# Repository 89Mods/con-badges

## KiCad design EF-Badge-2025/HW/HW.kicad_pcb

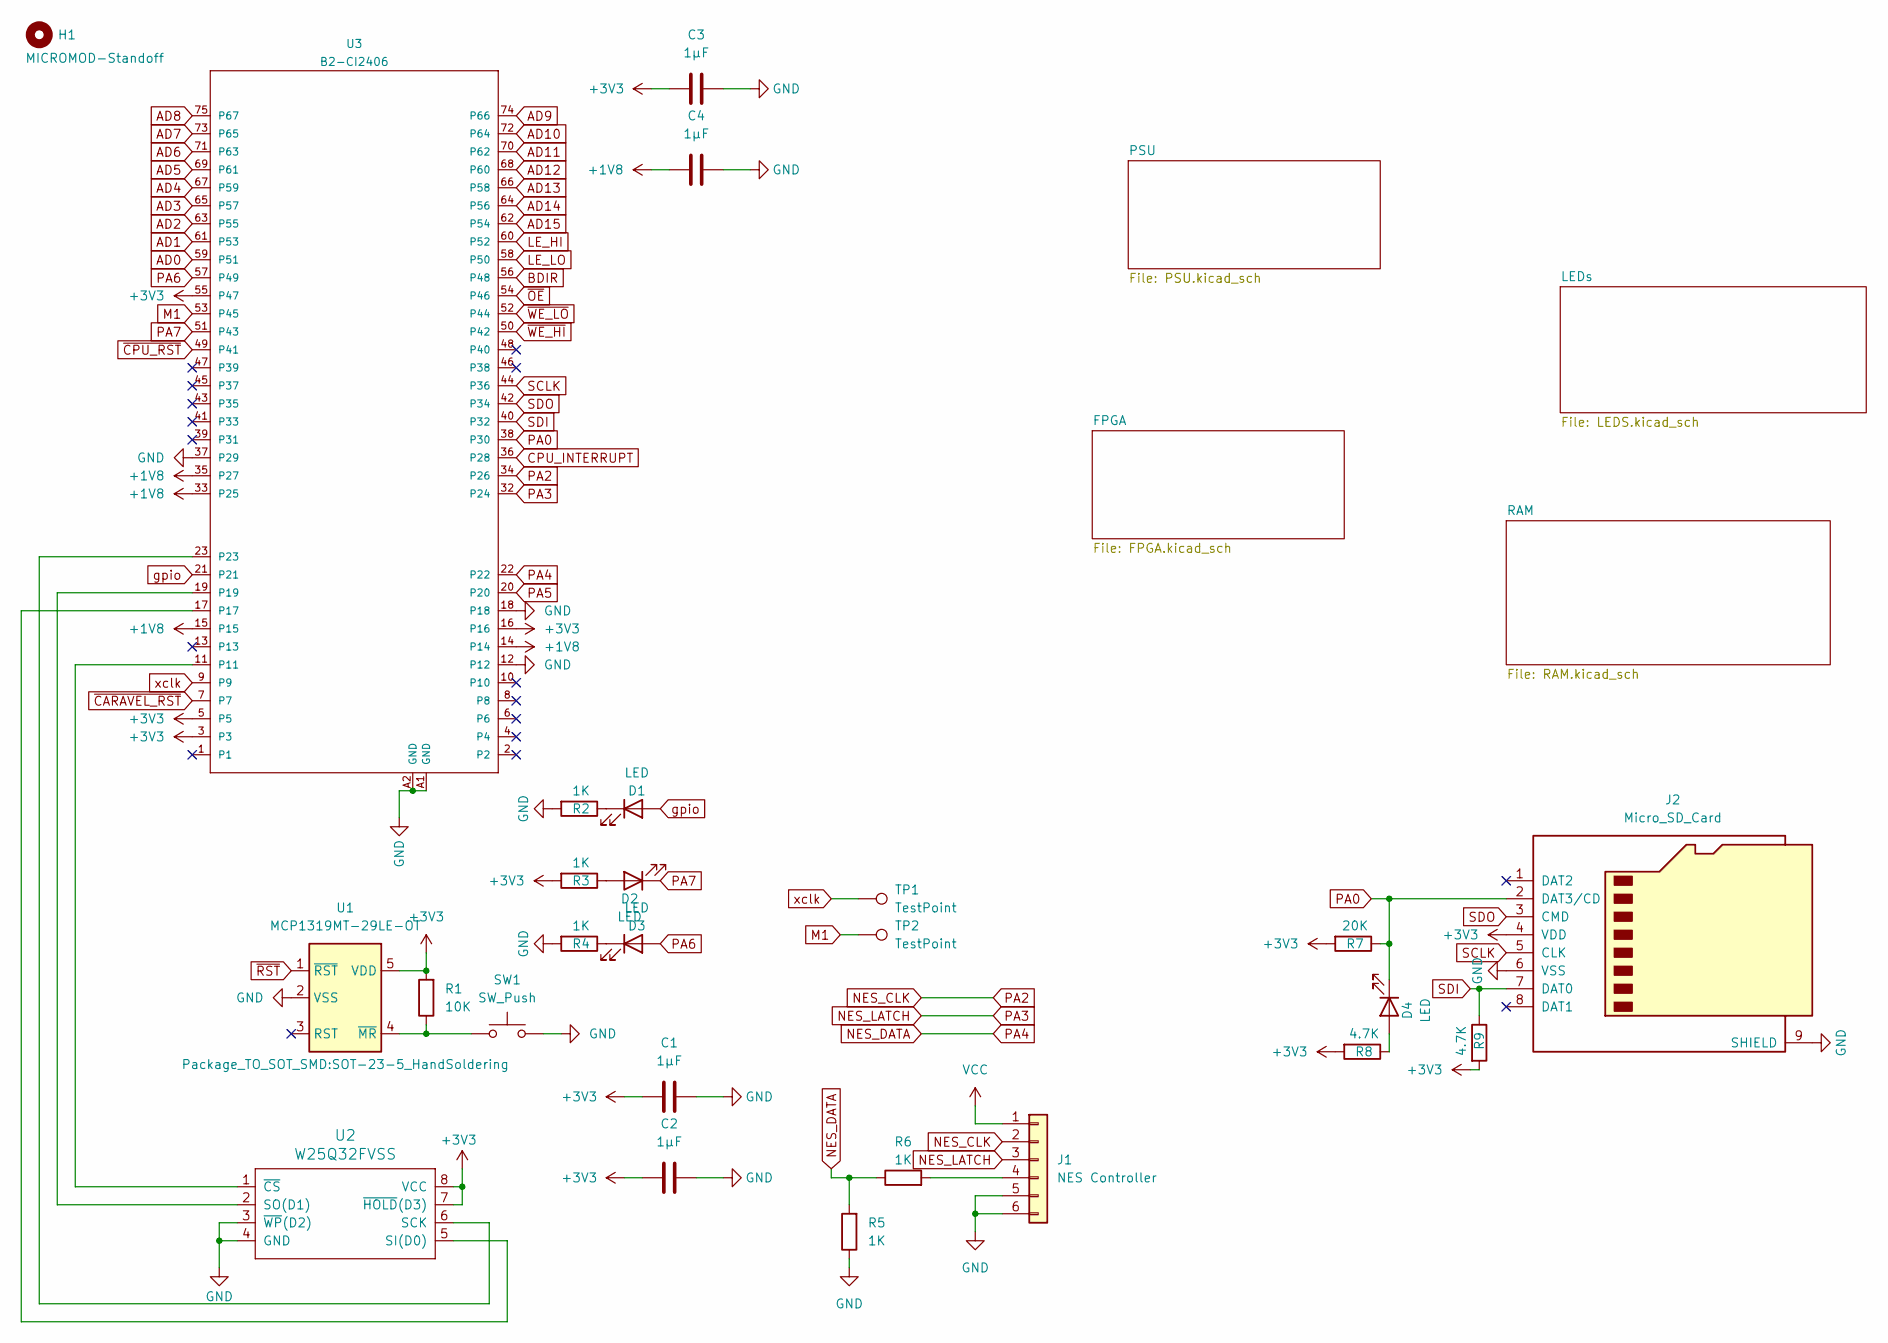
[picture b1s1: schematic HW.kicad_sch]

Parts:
C1, C2, C3, C4: 1µF; C_0805_2012Metric_Pad1.18x1.45mm_HandSolder
D1, D2, D3, D4: LED; LED_1206_3216Metric_Pad1.42x1.75mm_HandSolder
H1: MICROMOD-Standoff; MicroMod-Standoff
J1: NES Controller; PinSocket_1x06_P2.54mm_Vertical
J2: Micro_SD_Card; microSD_HC_Hirose_DM3AT-SF-PEJM5
R1: 10K; R_1206_3216Metric_Pad1.30x1.75mm_HandSolder
R2, R3, R4, R5, R6: 1K; R_1206_3216Metric_Pad1.30x1.75mm_HandSolder
R7: 20K; R_1206_3216Metric_Pad1.30x1.75mm_HandSolder
R8, R9: 4.7K; R_1206_3216Metric_Pad1.30x1.75mm_HandSolder
SW1: SW_Push; SW_PUSH_6mm
TP1, TP2: TestPoint; TestPoint_Pad_D1.0mm
U1: MCP1319MT-29LE-OT; SOT-23-5_HandSoldering
U2: W25Q32FVSS; DIP-8_W7.62mm; Part # W25Q32JVSSIQ
U3: B2-CI2406; M.2-CONNECTOR-E

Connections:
+1V8: C4.1, U3.14, U3.15, U3.33 (P25), U3.35 (P27); also elsewhere on the board
+3V3: C1.1, C2.1, C3.1, J2.4 (VDD), R1.2, R3.2, R7.2, R8.2, R9.2, U1.5 (VDD), U2.7 (~HOLD(D3)), U2.8 (VCC), U3.3, U3.5, U3.16, U3.55 (P47); also elsewhere on the board
AD0: U3.59 (P51); also elsewhere on the board
AD1: U3.61 (P53); also elsewhere on the board
AD2: U3.63 (P55); also elsewhere on the board
AD3: U3.65 (P57); also elsewhere on the board
AD4: U3.67 (P59); also elsewhere on the board
AD5: U3.69 (P61); also elsewhere on the board
AD6: U3.71 (P63); also elsewhere on the board
AD7: U3.73 (P65); also elsewhere on the board
AD8: U3.75 (P67); also elsewhere on the board
AD9: U3.74 (P66); also elsewhere on the board
AD10: U3.72 (P64); also elsewhere on the board
AD11: U3.70 (P62); also elsewhere on the board
AD12: U3.68 (P60); also elsewhere on the board
AD13: U3.66 (P58); also elsewhere on the board
AD14: U3.64 (P56); also elsewhere on the board
AD15: U3.62 (P54); also elsewhere on the board
BDIR: U3.56 (P48)
CPU_INTERRUPT: U3.36 (P28); also elsewhere on the board
GND: C1.2, C2.2, C3.2, C4.2, J1.5, J1.6, J2.6 (VSS), J2.9 (SHIELD), R2.2, R4.2, R5.1, SW1.2, U1.2 (VSS), U2.3 (~WP(D2)), U2.4 (GND), U3.12, U3.18, U3.37 (P29), U3.A1 (GND), U3.A2 (GND); also elsewhere on the board
LE_HI: U3.60 (P52); also elsewhere on the board
LE_LO: U3.58 (P50); also elsewhere on the board
M1: TP2.1, U3.53 (P45)
NES_CLK: J1.2, U3.34 (P26)
NES_DATA: R5.2, R6.1, U3.22
NES_LATCH: J1.3, U3.32 (P24)
unnamed: D1.1 (K), R2.1
unnamed: D2.2 (A), R3.1
unnamed: D3.1 (K), R4.1
unnamed: D4.2 (A), R8.1
unnamed: J1.4, R6.2
unnamed: R1.1, SW1.1, U1.4 (~MR)
unnamed: U2.6 (SCK), U3.23
unnamed: U2.5 (SI(D0)), U3.17
unnamed: U2.2 (SO(D1)), U3.19
unnamed: U2.1 (~CS), U3.11
PA0: D4.1 (K), J2.2 (DAT3/CD), R7.1, U3.38 (P30)
PA5: U3.20
PA6: D3.2 (A), U3.57 (P49)
PA7: D2.1 (K), U3.51 (P43)
SCLK: J2.5 (CLK), U3.44 (P36)
SDI: J2.7 (DAT0), R9.1, U3.40 (P32)
SDO: J2.3 (CMD), U3.42 (P34)
VCC: J1.1; also elsewhere on the board
gpio: D1.2 (A), U3.21; also elsewhere on the board
xclk: TP1.1, U3.9; also elsewhere on the board
~CARAVEL_RST: U3.7; also elsewhere on the board
~CPU_RST: U3.49 (P41); also elsewhere on the board
~OE: U3.54 (P46); also elsewhere on the board
~RST: U1.1 (~RST); also elsewhere on the board
~WE_HI: U3.50 (P42); also elsewhere on the board
~WE_LO: U3.52 (P44); also elsewhere on the board

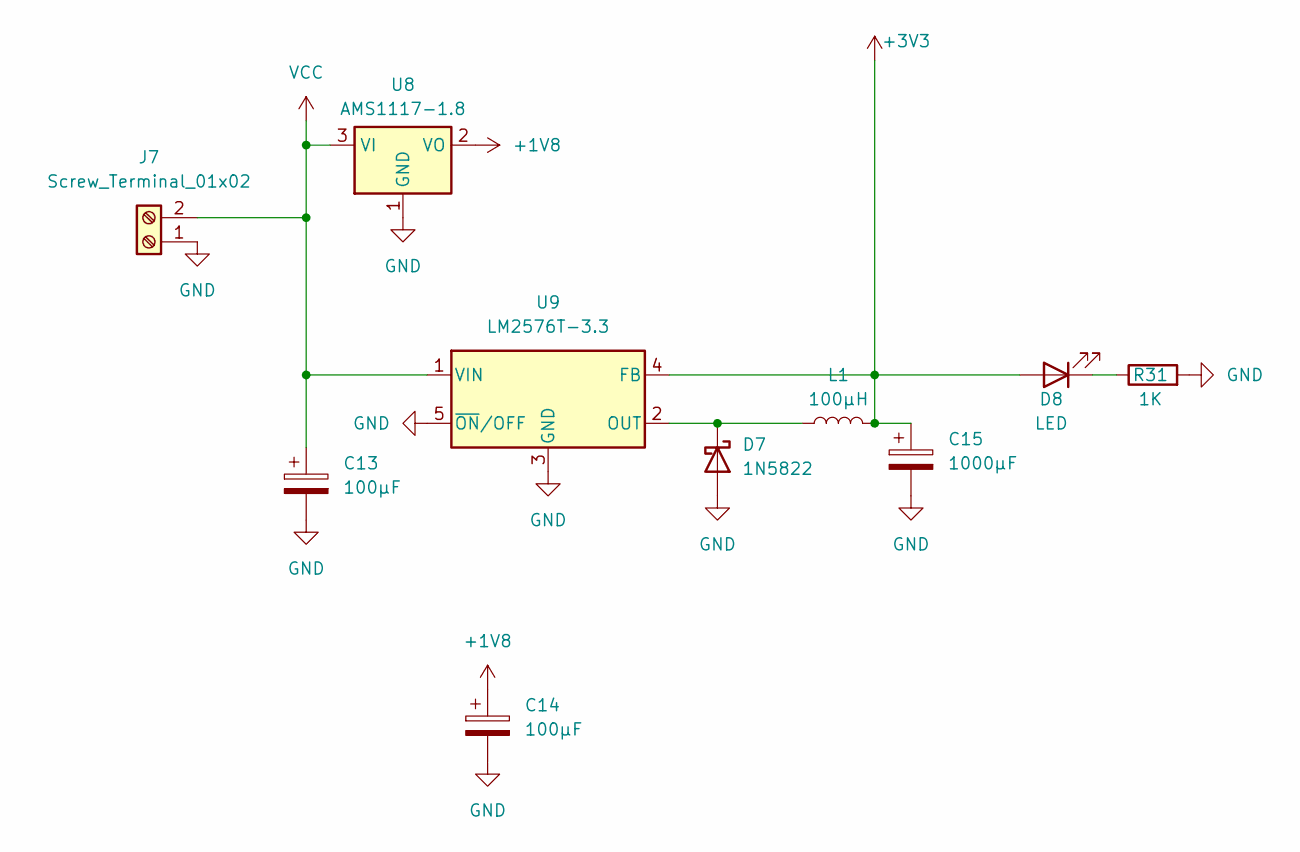
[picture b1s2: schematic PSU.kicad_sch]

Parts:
C13: 100µF; CP_Radial_D5.0mm_P2.50mm
C14: 100µF; CP_Elec_4x3
C15: 1000µF; CP_Radial_D6.3mm_P2.50mm
D7: 1N5822; D_DO-201AD_P15.24mm_Horizontal
D8: LED; LED_1206_3216Metric_Pad1.42x1.75mm_HandSolder
J7: Screw_Terminal_01x02; TerminalBlock_bornier-2_P5.08mm
L1: 100µH; L_Radial_D6.0mm_P4.00mm
R31: 1K; R_1206_3216Metric_Pad1.30x1.75mm_HandSolder
U8: AMS1117-1.8; SOT-223-3_TabPin2
U9: LM2576T-3.3; TO-220-5_Horizontal_TabDown_Fixed

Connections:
+1V8: C14.1, U8.2 (VO); also elsewhere on the board
+3V3: C15.1, D8.2 (A), L1.2, U9.4 (FB); also elsewhere on the board
GND: C13.2, C14.2, C15.2, D7.2 (A), J7.1, R31.2, U8.1 (GND), U9.3 (GND), U9.5 (~ON/OFF); also elsewhere on the board
unnamed: D7.1 (K), L1.1, U9.2 (OUT)
unnamed: D8.1 (K), R31.1
VCC: C13.1, J7.2, U8.3 (VI), U9.1 (VIN); also elsewhere on the board

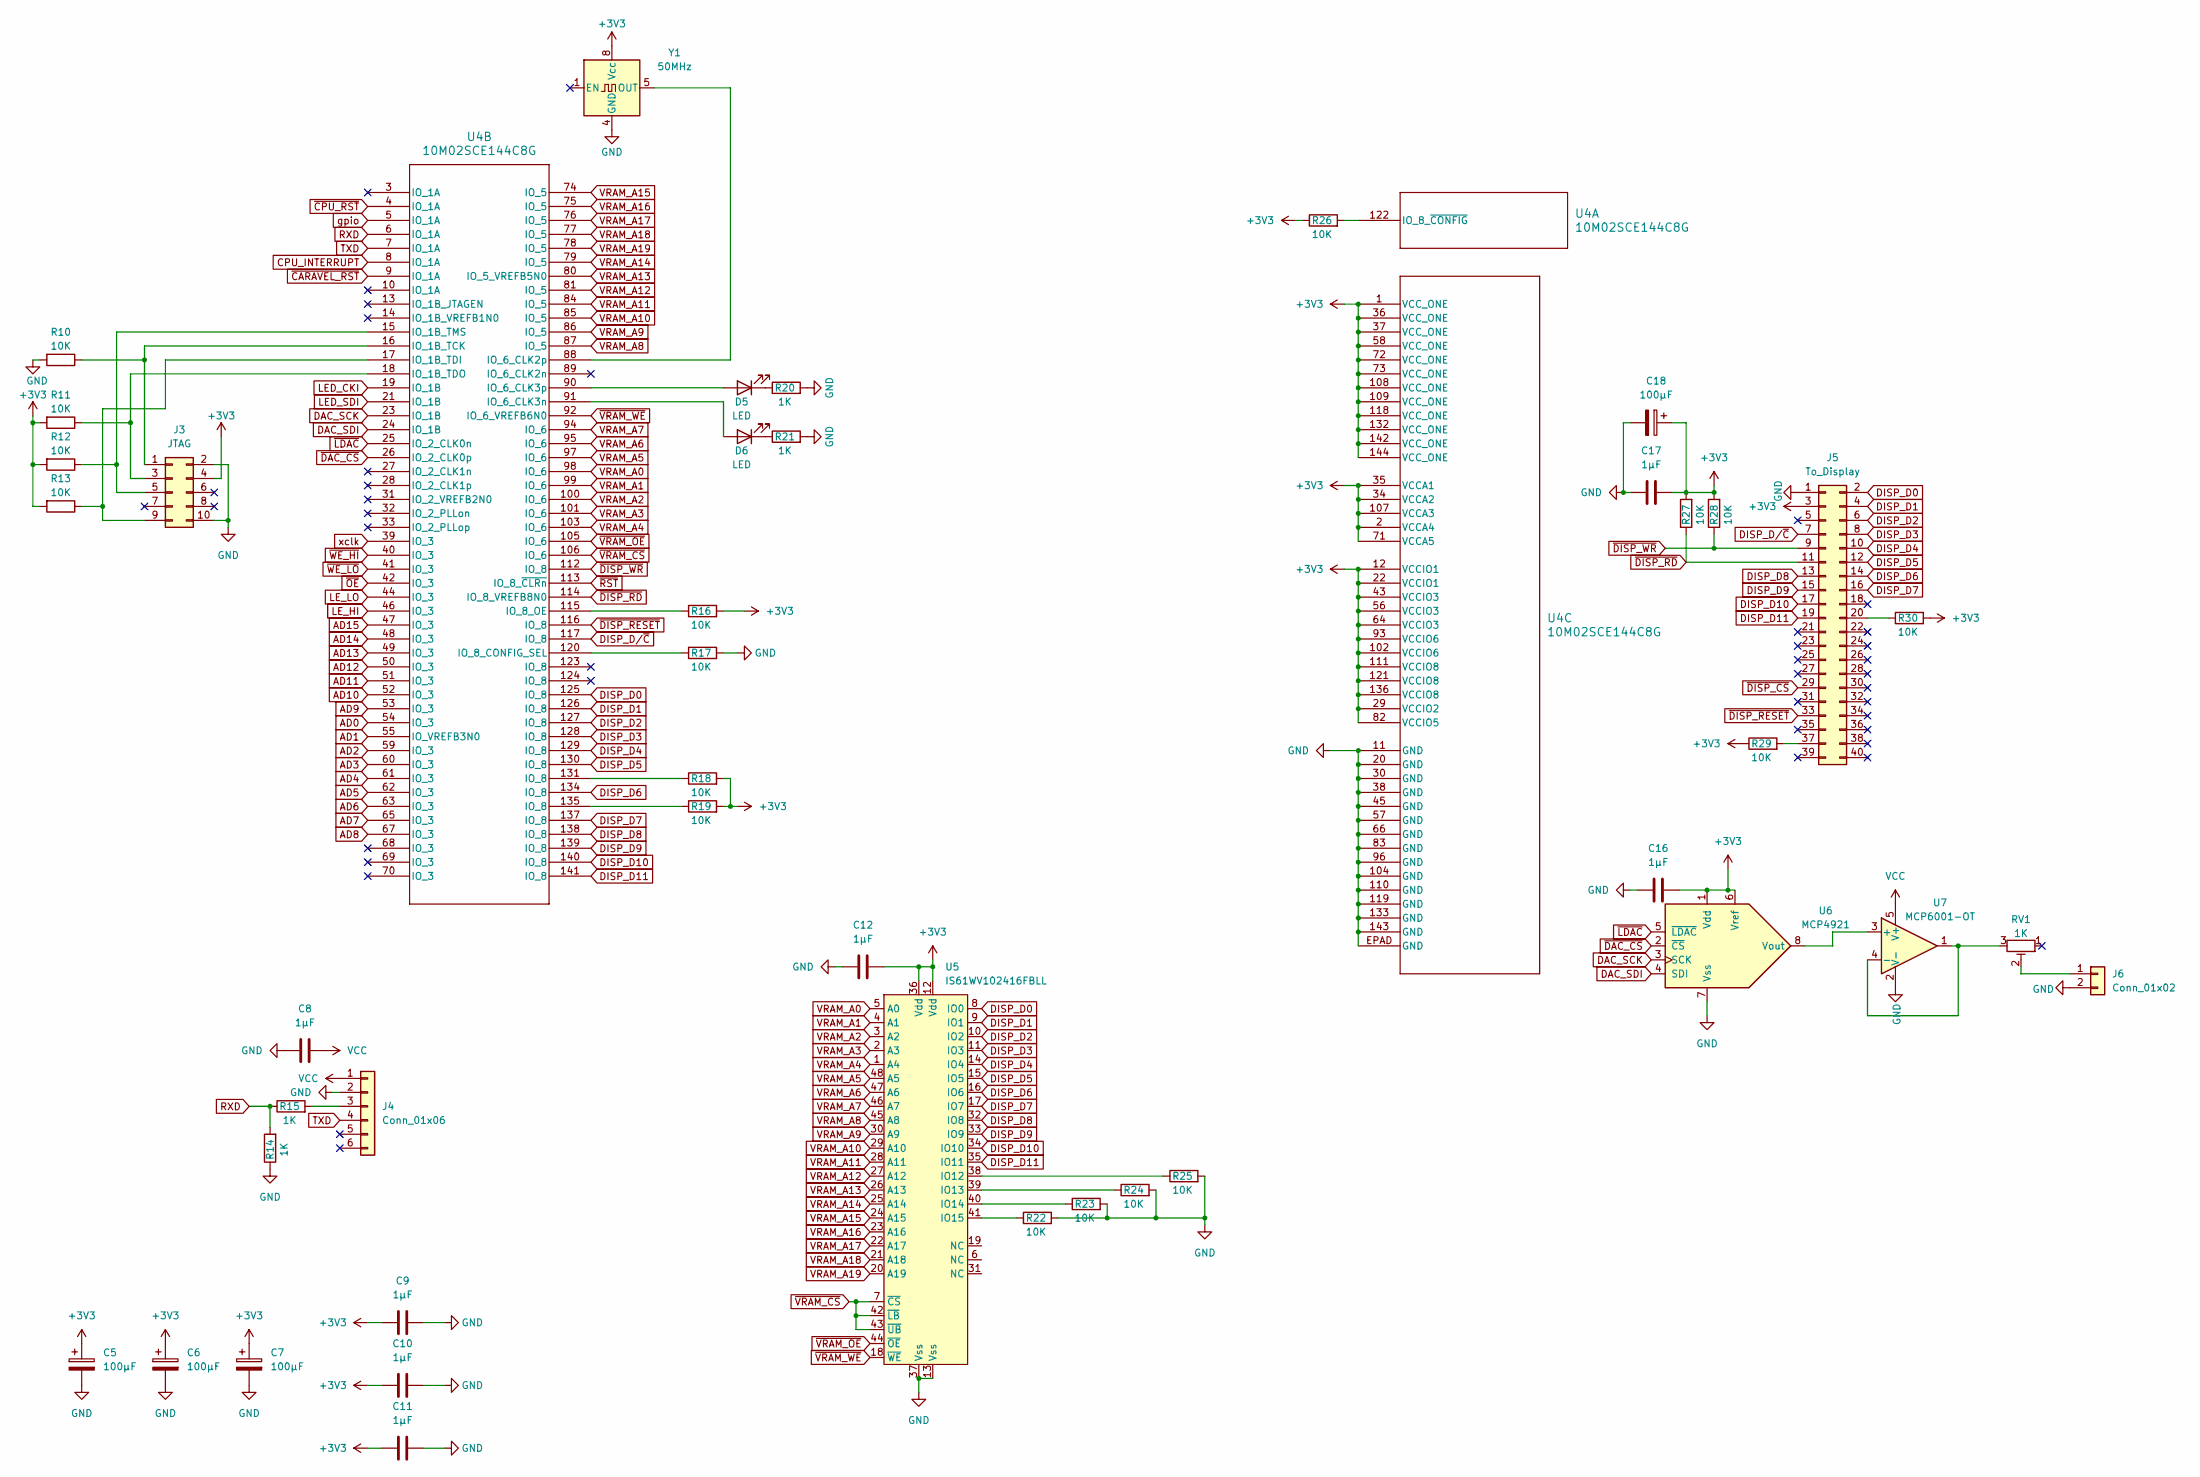
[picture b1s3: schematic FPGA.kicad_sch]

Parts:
C5, C6, C7, C18: 100µF; CP_Elec_4x3
C8, C9, C10, C11, C12, C16, C17: 1µF; C_0805_2012Metric_Pad1.18x1.45mm_HandSolder
D5, D6: LED; LED_1206_3216Metric_Pad1.42x1.75mm_HandSolder
J3: JTAG; PinHeader_2x05_P2.54mm_Vertical
J4: Conn_01x06; PinSocket_1x06_P2.54mm_Vertical
J5: To_Display; PinHeader_2x20_P2.54mm_Vertical
J6: Conn_01x02; PinHeader_1x02_P2.54mm_Vertical
R10, R11, R12, R13, R16, R17, R18, R19, R22, R23, R24, R25, R26, R27, R28, R29, R30: 10K; R_1206_3216Metric_Pad1.30x1.75mm_HandSolder
R14, R15, R20, R21: 1K; R_1206_3216Metric_Pad1.30x1.75mm_HandSolder
RV1: 1K; Potentiometer_ACP_CA9-V10_Vertical
U4: 10M02SCE144C8G; EQFP144_A-1.65-D2-4.0_INT
U5: IS61WV102416FBLL; TSOP-I-48_18.4x12mm_P0.5mm; Mouser 870-61WV12416FBL1TLI
U6: MCP4921; DIP-8_W7.62mm
U7: MCP6001-OT; SOT-23-5
Y1: 50MHz; Oscillator_DIP-8

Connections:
+3V3: C5.1, C6.1, C7.1, C9.1, C10.1, C11.1, C12.2, C16.2, C17.2, C18.1, J3.4, J5.3, R11.2, R12.2, R13.2, R16.2, R18.2, R19.2, R26.1, R27.2, R28.2, R29.1, R30.2, U4.1 (VCC_ONE), U4.2 (VCCA4), U4.12 (VCCIO1), U4.22 (VCCIO1), U4.29 (VCCIO2), U4.34 (VCCA2), U4.35 (VCCA1), U4.36 (VCC_ONE), U4.37 (VCC_ONE), U4.43 (VCCIO3), U4.56 (VCCIO3), U4.58 (VCC_ONE), U4.64 (VCCIO3), U4.71 (VCCA5), U4.72 (VCC_ONE), U4.73 (VCC_ONE), U4.82 (VCCIO5), U4.93 (VCCIO6), U4.102 (VCCIO6), U4.107 (VCCA3), U4.108 (VCC_ONE), U4.109 (VCC_ONE), U4.111 (VCCIO8), U4.118 (VCC_ONE), U4.121 (VCCIO8), U4.132 (VCC_ONE), U4.136 (VCCIO8), U4.142 (VCC_ONE), U4.144 (VCC_ONE), U5.12 (Vdd), U5.36 (Vdd), U6.1 (Vdd), U6.6 (Vref), Y1.8 (Vcc); also elsewhere on the board
AD0: U4.54 (IO_3); also elsewhere on the board
AD1: U4.55 (IO_VREFB3N0); also elsewhere on the board
AD2: U4.59 (IO_3); also elsewhere on the board
AD3: U4.60 (IO_3); also elsewhere on the board
AD4: U4.61 (IO_3); also elsewhere on the board
AD5: U4.62 (IO_3); also elsewhere on the board
AD6: U4.63 (IO_3); also elsewhere on the board
AD7: U4.65 (IO_3); also elsewhere on the board
AD8: U4.67 (IO_3); also elsewhere on the board
AD9: U4.53 (IO_3); also elsewhere on the board
AD10: U4.52 (IO_3); also elsewhere on the board
AD11: U4.51 (IO_3); also elsewhere on the board
AD12: U4.50 (IO_3); also elsewhere on the board
AD13: U4.49 (IO_3); also elsewhere on the board
AD14: U4.48 (IO_3); also elsewhere on the board
AD15: U4.47 (IO_3); also elsewhere on the board
CPU_INTERRUPT: U4.8 (IO_1A); also elsewhere on the board
DAC_SCK: U4.23 (IO_1B), U6.3 (SCK)
DAC_SDI: U4.24 (IO_1B), U6.4 (SDI)
DISP_D0: J5.2, U4.125 (IO_8), U5.8 (IO0)
DISP_D1: J5.4, U4.126 (IO_8), U5.9 (IO1)
DISP_D2: J5.6, U4.127 (IO_8), U5.10 (IO2)
DISP_D3: J5.8, U4.128 (IO_8), U5.11 (IO3)
DISP_D4: J5.10, U4.129 (IO_8), U5.14 (IO4)
DISP_D5: J5.12, U4.130 (IO_8), U5.15 (IO5)
DISP_D6: J5.14, U4.134 (IO_8), U5.16 (IO6)
DISP_D7: J5.16, U4.137 (IO_8), U5.17 (IO7)
DISP_D8: J5.13, U4.138 (IO_8), U5.32 (IO8)
DISP_D9: J5.15, U4.139 (IO_8), U5.33 (IO9)
DISP_D10: J5.17, U4.140 (IO_8), U5.34 (IO10)
DISP_D11: J5.19, U4.141 (IO_8), U5.35 (IO11)
DISP_D/~C: J5.7, U4.117 (IO_8)
GND: C5.2, C6.2, C7.2, C8.1, C9.2, C10.2, C11.2, C12.1, C16.1, C17.1, C18.2, J3.2, J3.10, J4.2, J5.1, J6.2, R10.2, R14.1, R17.2, R20.2, R21.2, R22.2, R23.2, R24.2, R25.2, U4.11 (GND), U4.20 (GND), U4.30 (GND), U4.38 (GND), U4.45 (GND), U4.57 (GND), U4.66 (GND), U4.83 (GND), U4.96 (GND), U4.104 (GND), U4.110 (GND), U4.119 (GND), U4.133 (GND), U4.143 (GND), U4.EPAD (GND), U5.13 (Vss), U5.37 (Vss), U6.7 (Vss), U7.2 (V-), Y1.4 (GND); also elsewhere on the board
LED_CKI: U4.19 (IO_1B); also elsewhere on the board
LED_SDI: U4.21 (IO_1B); also elsewhere on the board
LE_HI: U4.46 (IO_3); also elsewhere on the board
LE_LO: U4.44 (IO_3); also elsewhere on the board
unnamed: D5.2 (A), U4.90 (IO_6_CLK3p)
unnamed: D5.1 (K), R20.1
unnamed: D6.2 (A), U4.91 (IO_6_CLK3n)
unnamed: D6.1 (K), R21.1
unnamed: J3.1, R10.1, U4.16 (IO_1B_TCK)
unnamed: J3.3, R11.1, U4.18 (IO_1B_TDO)
unnamed: J3.5, R12.1, U4.15 (IO_1B_TMS)
unnamed: J3.9, R13.1, U4.17 (IO_1B_TDI)
unnamed: J4.3, R15.2
unnamed: J5.20, R30.1
unnamed: J5.37, R29.2
unnamed: J6.1, RV1.2
unnamed: R18.1, U4.131 (IO_8)
unnamed: R19.1, U4.135 (IO_8)
unnamed: R26.2, U4.122 (IO_8_~CONFIG)
unnamed: U4.88 (IO_6_CLK2p), Y1.5 (OUT)
unnamed: R17.1, U4.120 (IO_8_CONFIG_SEL)
unnamed: R16.1, U4.115 (IO_8_OE)
unnamed: R25.1, U5.38 (IO12)
unnamed: R24.1, U5.39 (IO13)
unnamed: R23.1, U5.40 (IO14)
unnamed: R22.1, U5.41 (IO15)
unnamed: U6.8 (Vout), U7.3 (+)
unnamed: RV1.3, U7.1, U7.4 (-)
RXD: R14.2, R15.1, U4.6 (IO_1A)
TXD: J4.4, U4.7 (IO_1A)
VCC: C8.2, J4.1, U7.5 (V+); also elsewhere on the board
VRAM_A0: U4.98 (IO_6), U5.5 (A0)
VRAM_A1: U4.99 (IO_6), U5.4 (A1)
VRAM_A2: U4.100 (IO_6), U5.3 (A2)
VRAM_A3: U4.101 (IO_6), U5.2 (A3)
VRAM_A4: U4.103 (IO_6), U5.1 (A4)
VRAM_A5: U4.97 (IO_6), U5.48 (A5)
VRAM_A6: U4.95 (IO_6), U5.47 (A6)
VRAM_A7: U4.94 (IO_6), U5.46 (A7)
VRAM_A8: U4.87 (IO_5), U5.45 (A8)
VRAM_A9: U4.86 (IO_5), U5.30 (A9)
VRAM_A10: U4.85 (IO_5), U5.29 (A10)
VRAM_A11: U4.84 (IO_5), U5.28 (A11)
VRAM_A12: U4.81 (IO_5), U5.27 (A12)
VRAM_A13: U4.80 (IO_5_VREFB5N0), U5.26 (A13)
VRAM_A14: U4.79 (IO_5), U5.25 (A14)
VRAM_A15: U4.74 (IO_5), U5.24 (A15)
VRAM_A16: U4.75 (IO_5), U5.23 (A16)
VRAM_A17: U4.76 (IO_5), U5.22 (A17)
VRAM_A18: U4.77 (IO_5), U5.21 (A18)
VRAM_A19: U4.78 (IO_5), U5.20 (A19)
gpio: U4.5 (IO_1A); also elsewhere on the board
xclk: U4.39 (IO_3); also elsewhere on the board
~CARAVEL_RST: U4.9 (IO_1A); also elsewhere on the board
~CPU_RST: U4.4 (IO_1A); also elsewhere on the board
~DAC_CS: U4.26 (IO_2_CLK0p), U6.2 (~CS)
~DISP_CS: J5.29
~DISP_RD: J5.11, R27.1, U4.114 (IO_8_VREFB8N0)
~DISP_RESET: J5.33, U4.116 (IO_8)
~DISP_WR: J5.9, R28.1, U4.112 (IO_8)
~LDAC: U4.25 (IO_2_CLK0n), U6.5 (~LDAC)
~OE: U4.42 (IO_3); also elsewhere on the board
~RST: U4.113 (IO_8_~CLRn); also elsewhere on the board
~VRAM_CS: U4.106 (IO_6), U5.7 (~CS), U5.42 (~LB), U5.43 (~UB)
~VRAM_OE: U4.105 (IO_6), U5.44 (~OE)
~VRAM_WE: U4.92 (IO_6_VREFB6N0), U5.18 (~WE)
~WE_HI: U4.40 (IO_3); also elsewhere on the board
~WE_LO: U4.41 (IO_3); also elsewhere on the board

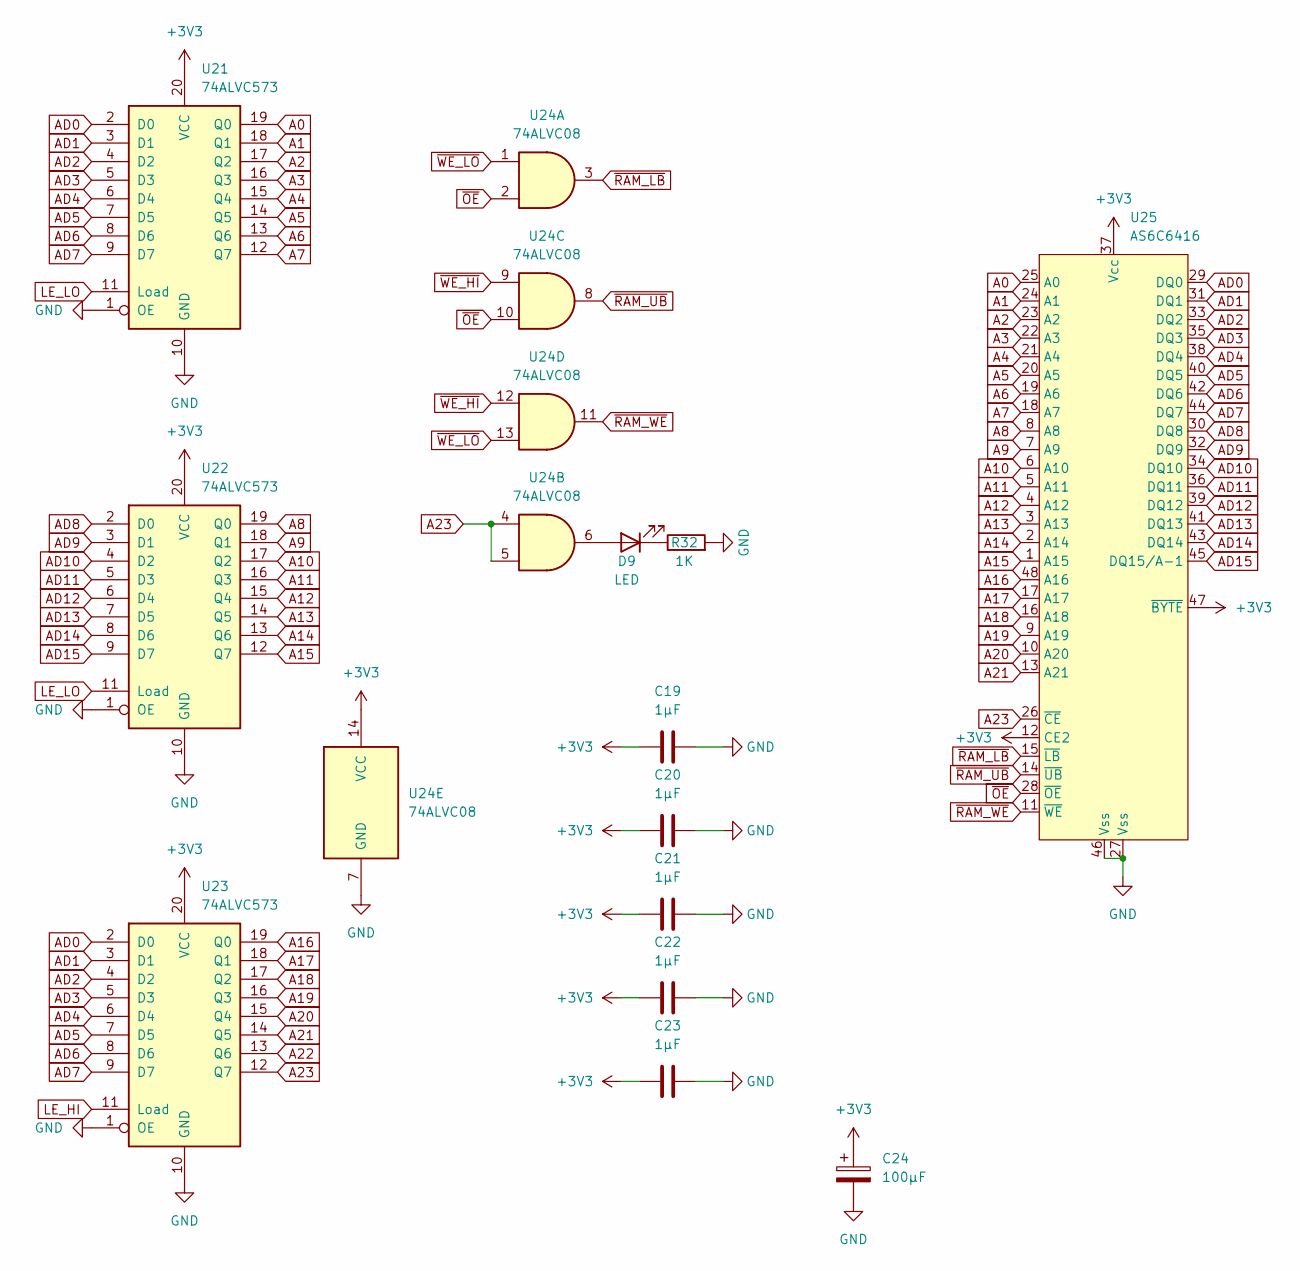
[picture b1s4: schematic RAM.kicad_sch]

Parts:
C19, C20, C21, C22, C23: 1µF; C_0805_2012Metric_Pad1.18x1.45mm_HandSolder
C24: 100µF; CP_Elec_4x3
D9: LED; LED_1206_3216Metric_Pad1.42x1.75mm_HandSolder
R32: 1K; R_1206_3216Metric_Pad1.30x1.75mm_HandSolder
U21, U22, U23: 74ALVC573; TSSOP-20_4.4x6.5mm_P0.65mm; Mouser 771-ALVC573PW118
U24: 74ALVC08; SOIC-14_3.9x8.7mm_P1.27mm; Mouser 771-ALVC08D118
U25: AS6C6416; TSOP-I-48_18.4x12mm_P0.5mm; Mouser 913-AS6C6416-55TIN

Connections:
+3V3: C19.1, C20.1, C21.1, C22.1, C23.1, C24.1, U21.20 (VCC), U22.20 (VCC), U23.20 (VCC), U24.14 (VCC), U25.12 (CE2), U25.37 (Vcc), U25.47 (~BYTE); also elsewhere on the board
A0: U21.19 (Q0), U25.25 (A0)
A1: U21.18 (Q1), U25.24 (A1)
A2: U21.17 (Q2), U25.23 (A2)
A3: U21.16 (Q3), U25.22 (A3)
A4: U21.15 (Q4), U25.21 (A4)
A5: U21.14 (Q5), U25.20 (A5)
A6: U21.13 (Q6), U25.19 (A6)
A7: U21.12 (Q7), U25.18 (A7)
A8: U22.19 (Q0), U25.8 (A8)
A9: U22.18 (Q1), U25.7 (A9)
A10: U22.17 (Q2), U25.6 (A10)
A11: U22.16 (Q3), U25.5 (A11)
A12: U22.15 (Q4), U25.4 (A12)
A13: U22.14 (Q5), U25.3 (A13)
A14: U22.13 (Q6), U25.2 (A14)
A15: U22.12 (Q7), U25.1 (A15)
A16: U23.19 (Q0), U25.48 (A16)
A17: U23.18 (Q1), U25.17 (A17)
A18: U23.17 (Q2), U25.16 (A18)
A19: U23.16 (Q3), U25.9 (A19)
A20: U23.15 (Q4), U25.10 (A20)
A21: U23.14 (Q5), U25.13 (A21)
A22: U23.13 (Q6)
A23: U23.12 (Q7), U24.4, U24.5, U25.26 (~CE)
AD0: U21.2 (D0), U23.2 (D0), U25.29 (DQ0); also elsewhere on the board
AD1: U21.3 (D1), U23.3 (D1), U25.31 (DQ1); also elsewhere on the board
AD2: U21.4 (D2), U23.4 (D2), U25.33 (DQ2); also elsewhere on the board
AD3: U21.5 (D3), U23.5 (D3), U25.35 (DQ3); also elsewhere on the board
AD4: U21.6 (D4), U23.6 (D4), U25.38 (DQ4); also elsewhere on the board
AD5: U21.7 (D5), U23.7 (D5), U25.40 (DQ5); also elsewhere on the board
AD6: U21.8 (D6), U23.8 (D6), U25.42 (DQ6); also elsewhere on the board
AD7: U21.9 (D7), U23.9 (D7), U25.44 (DQ7); also elsewhere on the board
AD8: U22.2 (D0), U25.30 (DQ8); also elsewhere on the board
AD9: U22.3 (D1), U25.32 (DQ9); also elsewhere on the board
AD10: U22.4 (D2), U25.34 (DQ10); also elsewhere on the board
AD11: U22.5 (D3), U25.36 (DQ11); also elsewhere on the board
AD12: U22.6 (D4), U25.39 (DQ12); also elsewhere on the board
AD13: U22.7 (D5), U25.41 (DQ13); also elsewhere on the board
AD14: U22.8 (D6), U25.43 (DQ14); also elsewhere on the board
AD15: U22.9 (D7), U25.45 (DQ15/A-1); also elsewhere on the board
GND: C19.2, C20.2, C21.2, C22.2, C23.2, C24.2, R32.2, U21.1 (OE), U21.10 (GND), U22.1 (OE), U22.10 (GND), U23.1 (OE), U23.10 (GND), U24.7 (GND), U25.27 (Vss), U25.46 (Vss); also elsewhere on the board
LE_HI: U23.11 (Load); also elsewhere on the board
LE_LO: U21.11 (Load), U22.11 (Load); also elsewhere on the board
unnamed: D9.2 (A), U24.6
unnamed: D9.1 (K), R32.1
~OE: U24.2, U24.10, U25.28 (~OE); also elsewhere on the board
~RAM_LB: U24.3, U25.15 (~LB)
~RAM_UB: U24.8, U25.14 (~UB)
~RAM_WE: U24.11, U25.11 (~WE)
~WE_HI: U24.9, U24.12; also elsewhere on the board
~WE_LO: U24.1, U24.13; also elsewhere on the board

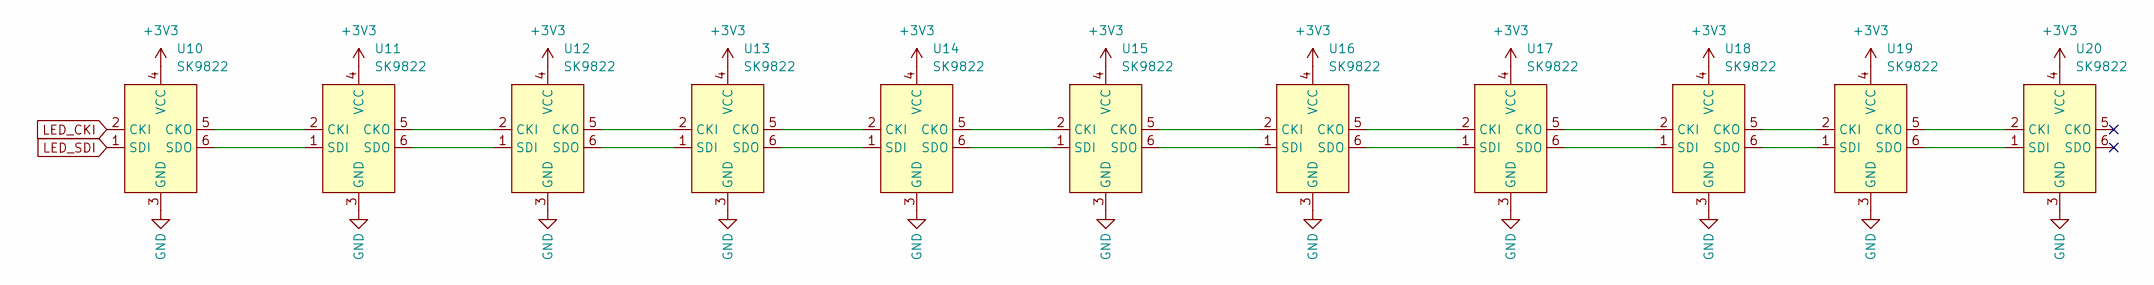
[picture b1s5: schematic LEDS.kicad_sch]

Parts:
U10, U11, U12, U13, U14, U15, U16, U17, U18, U19, U20: SK9822; SK9822-EC20

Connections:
+3V3: U10.4 (VCC), U11.4 (VCC), U12.4 (VCC), U13.4 (VCC), U14.4 (VCC), U15.4 (VCC), U16.4 (VCC), U17.4 (VCC), U18.4 (VCC), U19.4 (VCC), U20.4 (VCC); also elsewhere on the board
GND: U10.3 (GND), U11.3 (GND), U12.3 (GND), U13.3 (GND), U14.3 (GND), U15.3 (GND), U16.3 (GND), U17.3 (GND), U18.3 (GND), U19.3 (GND), U20.3 (GND); also elsewhere on the board
LED_CKI: U10.2 (CKI); also elsewhere on the board
LED_SDI: U10.1 (SDI); also elsewhere on the board
unnamed: U10.5 (CKO), U11.2 (CKI)
unnamed: U10.6 (SDO), U11.1 (SDI)
unnamed: U11.5 (CKO), U12.2 (CKI)
unnamed: U11.6 (SDO), U12.1 (SDI)
unnamed: U12.5 (CKO), U13.2 (CKI)
unnamed: U12.6 (SDO), U13.1 (SDI)
unnamed: U13.5 (CKO), U14.2 (CKI)
unnamed: U13.6 (SDO), U14.1 (SDI)
unnamed: U14.5 (CKO), U15.2 (CKI)
unnamed: U14.6 (SDO), U15.1 (SDI)
unnamed: U15.5 (CKO), U16.2 (CKI)
unnamed: U15.6 (SDO), U16.1 (SDI)
unnamed: U16.5 (CKO), U17.2 (CKI)
unnamed: U16.6 (SDO), U17.1 (SDI)
unnamed: U17.5 (CKO), U18.2 (CKI)
unnamed: U17.6 (SDO), U18.1 (SDI)
unnamed: U18.5 (CKO), U19.2 (CKI)
unnamed: U18.6 (SDO), U19.1 (SDI)
unnamed: U19.5 (CKO), U20.2 (CKI)
unnamed: U19.6 (SDO), U20.1 (SDI)

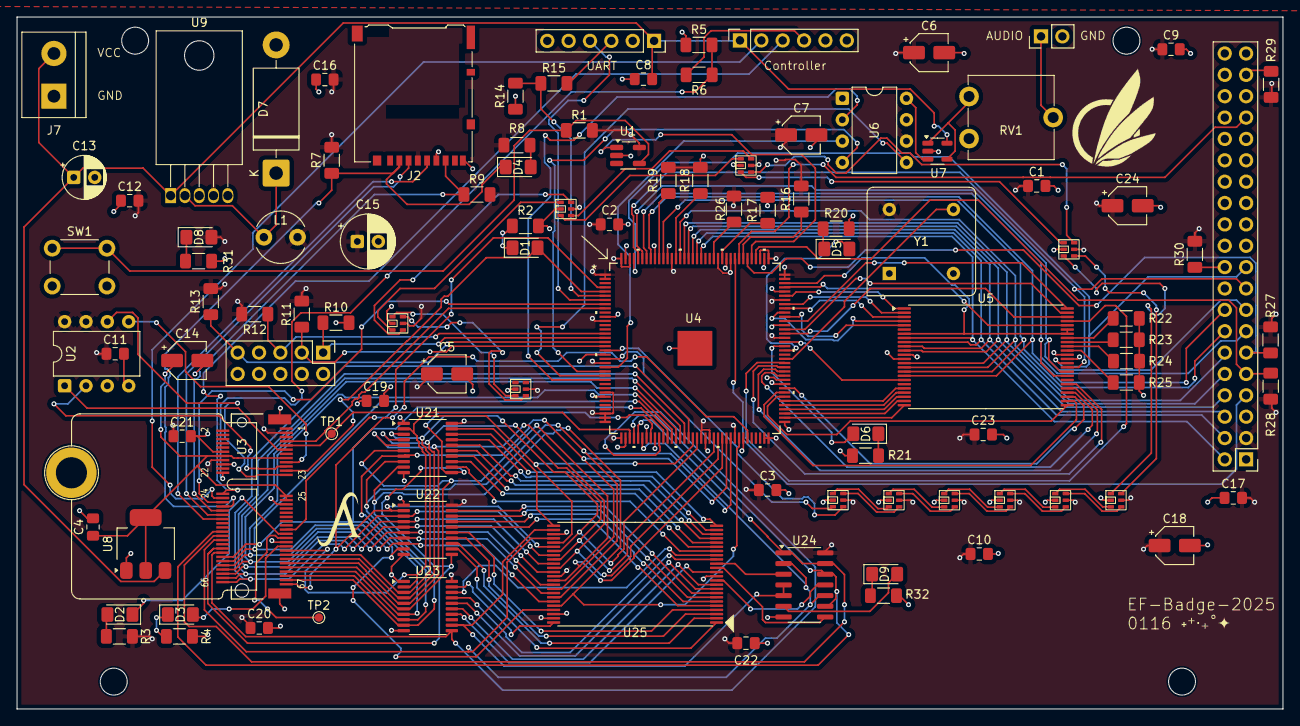
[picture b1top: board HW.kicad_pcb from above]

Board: 4 copper layers, 150.5 x 82.3 mm, 104 parts (0 on the bottom side), 172 nets.

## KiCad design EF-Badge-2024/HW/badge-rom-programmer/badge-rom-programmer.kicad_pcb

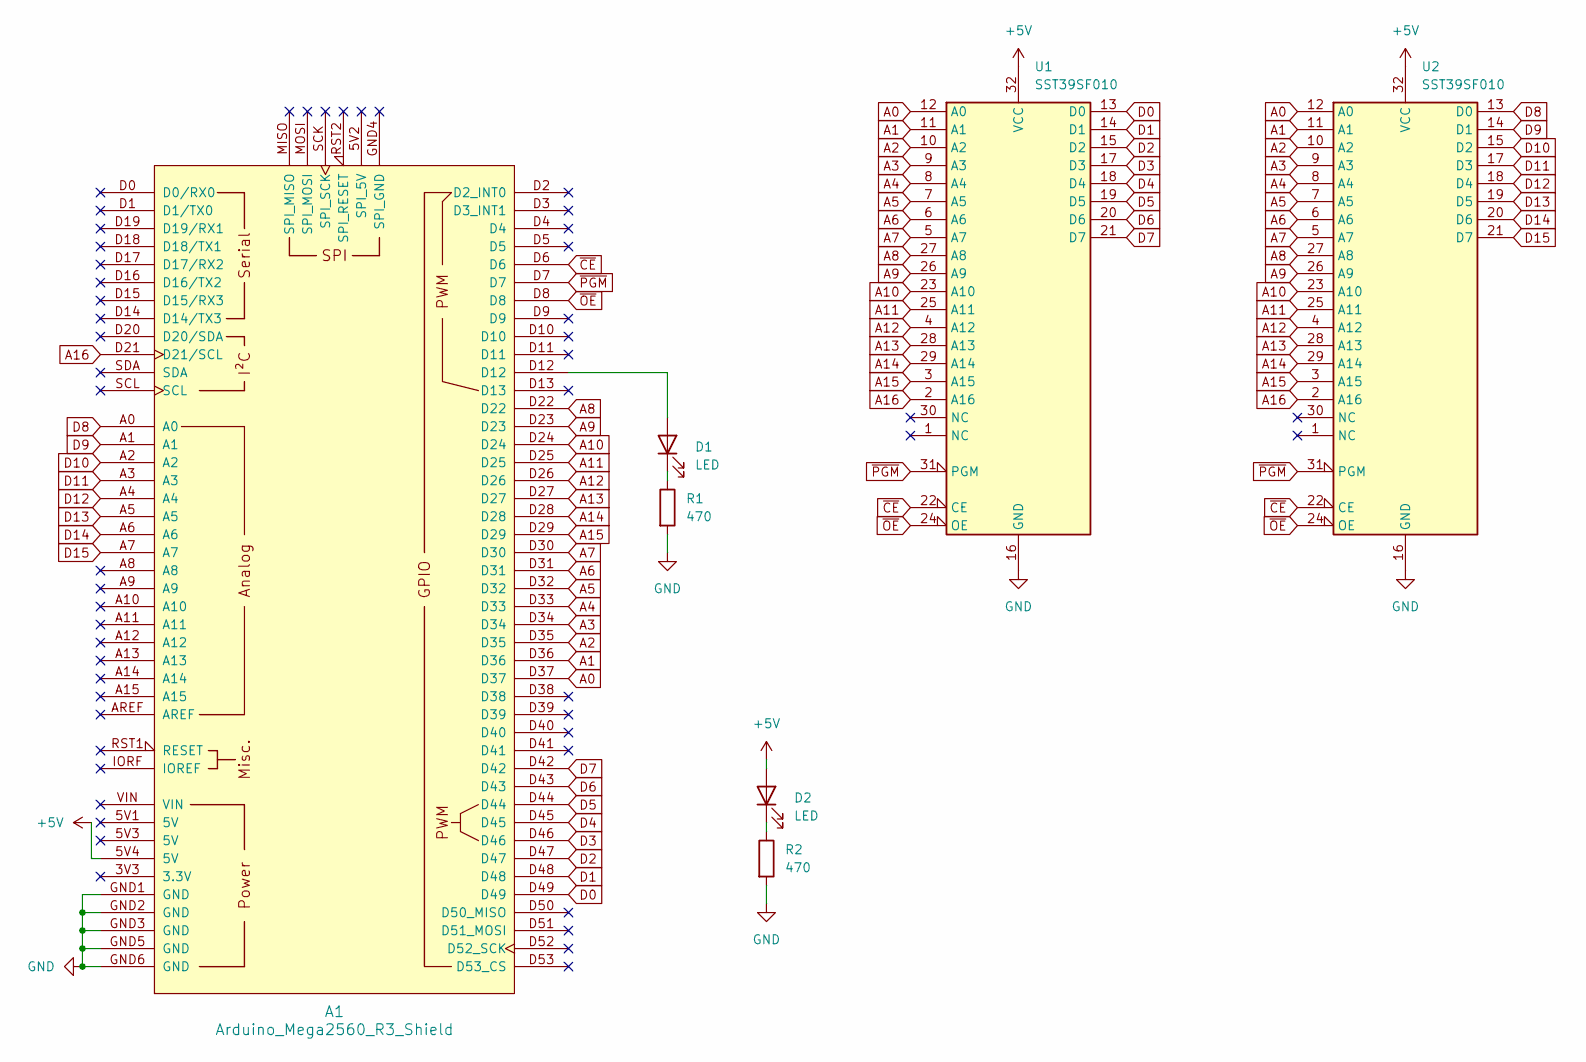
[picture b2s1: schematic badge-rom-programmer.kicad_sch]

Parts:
A1: Arduino_Mega2560_R3_Shield
D1, D2: LED; LED_D3.0mm
R1, R2: 470; R_Axial_DIN0204_L3.6mm_D1.6mm_P7.62mm_Horizontal
U1, U2: SST39SF010; PLCC-32_THT-Socket

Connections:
+5V: A1.5V4 (5V), D2.2 (A), U1.32 (VCC), U2.32 (VCC)
A0: A1.D37, U1.12 (A0), U2.12 (A0)
A1: A1.D36, U1.11 (A1), U2.11 (A1)
A2: A1.D35, U1.10 (A2), U2.10 (A2)
A3: A1.D34, U1.9 (A3), U2.9 (A3)
A4: A1.D33, U1.8 (A4), U2.8 (A4)
A5: A1.D32, U1.7 (A5), U2.7 (A5)
A6: A1.D31, U1.6 (A6), U2.6 (A6)
A7: A1.D30, U1.5 (A7), U2.5 (A7)
A8: A1.D22, U1.27 (A8), U2.27 (A8)
A9: A1.D23, U1.26 (A9), U2.26 (A9)
A10: A1.D24, U1.23 (A10), U2.23 (A10)
A11: A1.D25, U1.25 (A11), U2.25 (A11)
A12: A1.D26, U1.4 (A12), U2.4 (A12)
A13: A1.D27, U1.28 (A13), U2.28 (A13)
A14: A1.D28, U1.29 (A14), U2.29 (A14)
A15: A1.D29, U1.3 (A15), U2.3 (A15)
A16: A1.D21 (D21/SCL), U1.2 (A16), U2.2 (A16)
D0: A1.D49, U1.13 (D0)
D1: A1.D48, U1.14 (D1)
D2: A1.D47, U1.15 (D2)
D3: A1.D46, U1.17 (D3)
D4: A1.D45, U1.18 (D4)
D5: A1.D44, U1.19 (D5)
D6: A1.D43, U1.20 (D6)
D7: A1.D42, U1.21 (D7)
D8: A1.A0, U2.13 (D0)
D9: A1.A1, U2.14 (D1)
D10: A1.A2, U2.15 (D2)
D11: A1.A3, U2.17 (D3)
D12: A1.A4, U2.18 (D4)
D13: A1.A5, U2.19 (D5)
D14: A1.A6, U2.20 (D6)
D15: A1.A7, U2.21 (D7)
GND: A1.GND1 (GND), A1.GND2 (GND), A1.GND3 (GND), A1.GND5 (GND), A1.GND6 (GND), R1.2, R2.2, U1.16 (GND), U2.16 (GND)
unnamed: A1.D12, D1.2 (A)
unnamed: D1.1 (K), R1.1
unnamed: D2.1 (K), R2.1
~CE: A1.D6, U1.22 (CE), U2.22 (CE)
~OE: A1.D8, U1.24 (OE), U2.24 (OE)
~PGM: A1.D7, U1.31 (PGM), U2.31 (PGM)

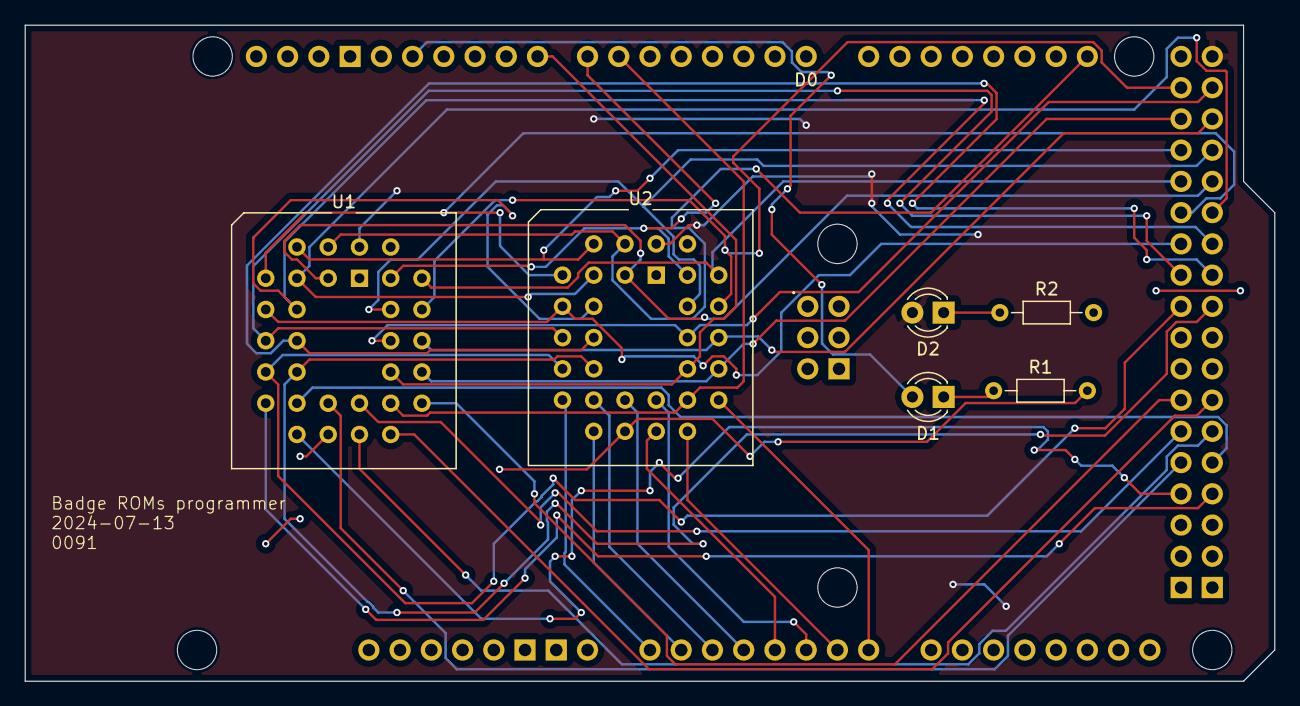
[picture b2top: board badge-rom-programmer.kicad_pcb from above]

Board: 2 copper layers, 101.6 x 53.3 mm, 7 parts (0 on the bottom side), 41 nets.

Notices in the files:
EF-Badge-2025/FPGA_SRC/VLIWBadgeCtrl.qsf:
Copyright (C) 2025  Altera Corporation. All rights reserved.
